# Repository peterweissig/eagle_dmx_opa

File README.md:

# project_opa
DMX control unit, based on atmel 32-bit controller

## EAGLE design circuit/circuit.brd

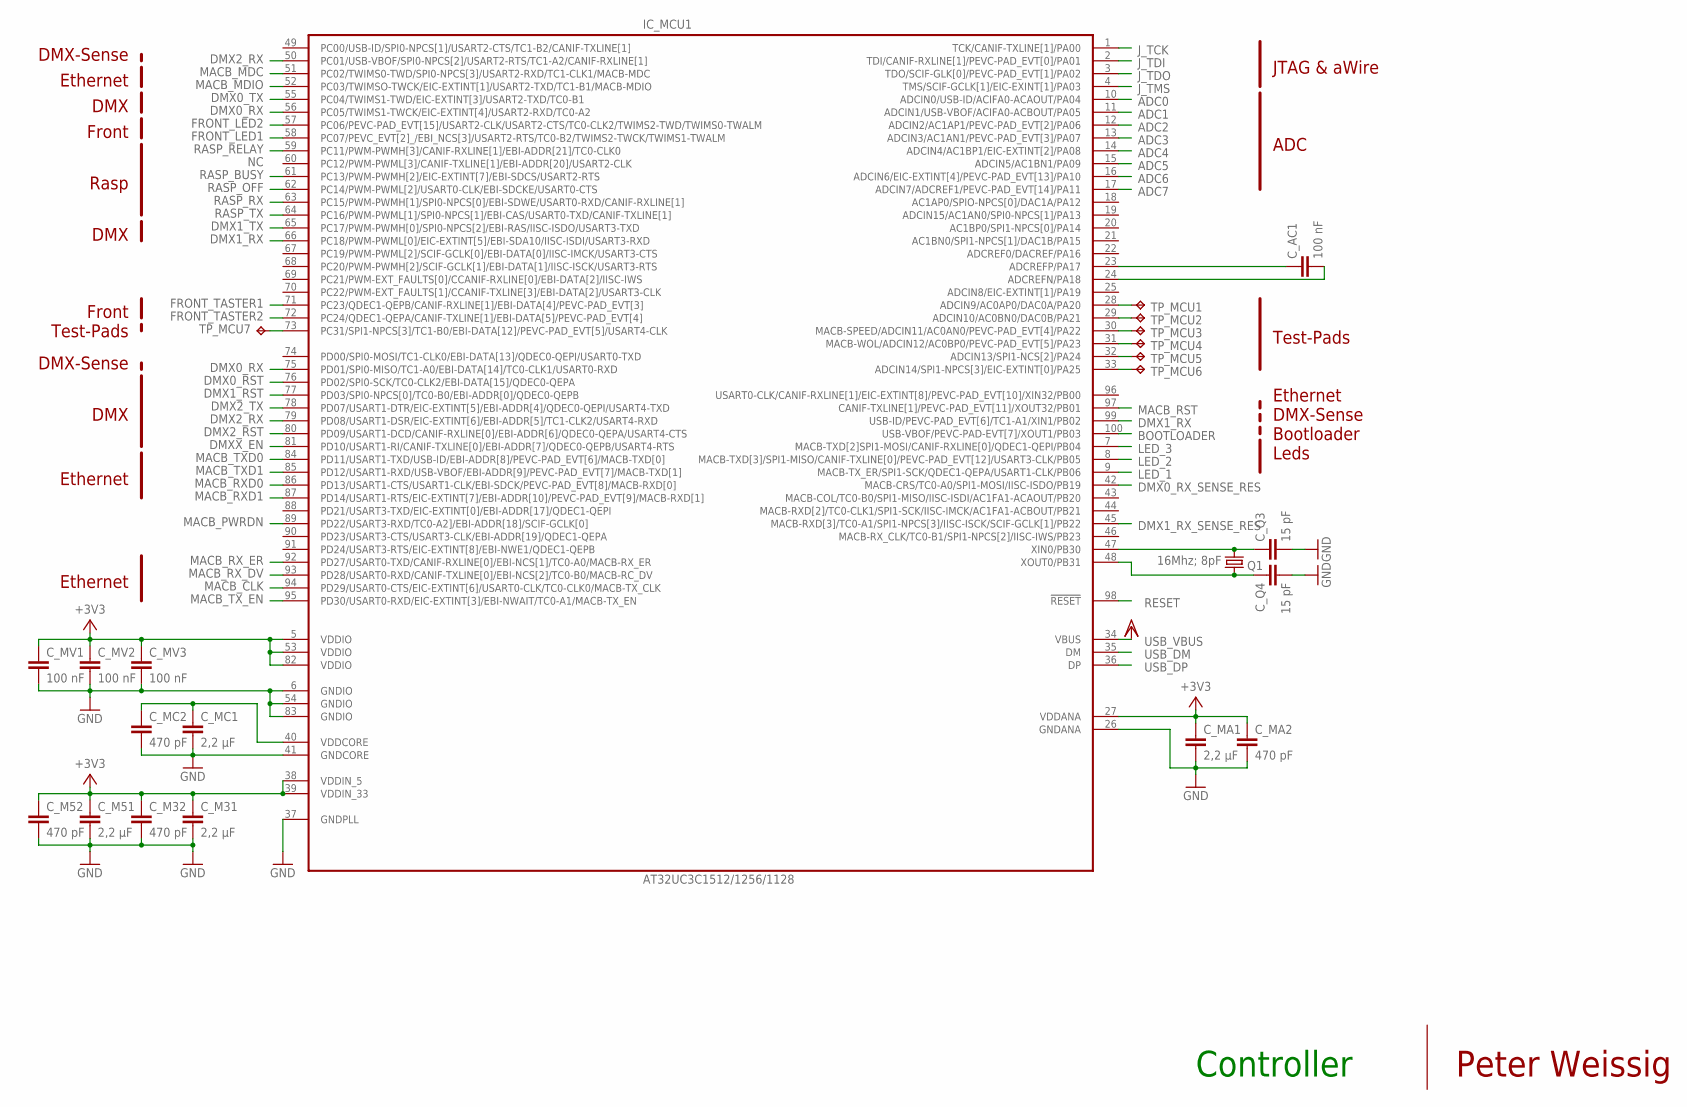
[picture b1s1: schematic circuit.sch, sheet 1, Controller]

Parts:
C_AC1: 100 nF; C0603K
C_M31, C_M51: 2,2 µF; C0603K
C_M32, C_M52: 470 pF; C0603K
C_MA1: 2,2 µF; C0603K
C_MA2: 470 pF; C0603K
C_MC1: 2,2 µF; C0603K
C_MC2: 470 pF; C0603K
C_MV1, C_MV2, C_MV3: 100 nF; C0603K
C_Q3, C_Q4: 15 pF; C0603K
IC_MCU1: AT32UC3C1512/1256/1128; TQFP100
Q1: 16Mhz; 8pF; NX5032
TP_MCU1, TP_MCU2, TP_MCU3, TP_MCU4, TP_MCU5, TP_MCU6, TP_MCU7: TPTP15R; TP15R

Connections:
+3V3: C_M31.1, C_M32.1, C_M51.1, C_M52.1, C_MA1.1, C_MA2.1, C_MV1.1, C_MV2.1, C_MV3.1, IC_MCU1.5 (VDDIO), IC_MCU1.27 (VDDANA), IC_MCU1.38 (VDDIN_5), IC_MCU1.39 (VDDIN_33), IC_MCU1.53 (VDDIO), IC_MCU1.82 (VDDIO); also elsewhere on the board
ADC0: IC_MCU1.10 (ADCIN0/USB-ID/ACIFA0-ACAOUT/PA04); also elsewhere on the board
ADC1: IC_MCU1.11 (ADCIN1/USB-VBOF/ACIFA0-ACBOUT/PA05); also elsewhere on the board
ADC2: IC_MCU1.12 (ADCIN2/AC1AP1/PEVC-PAD_EVT[2]/PA06); also elsewhere on the board
ADC3: IC_MCU1.13 (ADCIN3/AC1AN1/PEVC-PAD_EVT[3]/PA07); also elsewhere on the board
ADC4: IC_MCU1.14 (ADCIN4/AC1BP1/EIC-EXTINT[2]/PA08); also elsewhere on the board
ADC5: IC_MCU1.15 (ADCIN5/AC1BN1/PA09); also elsewhere on the board
ADC6: IC_MCU1.16 (ADCIN6/EIC-EXTINT[4]/PEVC-PAD_EVT[13]/P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); also elsewhere on the board
ADC7: IC_MCU1.17 (ADCIN7/ADCREF1/PEVC-PAD_EVT[14]/PA11); also elsewhere on the board
BOOTLOADER: IC_MCU1.100 (USB-VBOF/PEVC-PAD-EVT[7]/XOUT1/PB03); also elsewhere on the board
DMX0_RST: IC_MCU1.76 (PD02/SPI0-SCK/TC0-CLK2/EBI-DATA[15]/QDE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); also elsewhere on the board
DMX0_RX: IC_MCU1.56 (PC05/TWIMS1-TWCK/EIC-EXTINT[4]/USART2-R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), IC_MCU1.75 (PD01/SPI0-MISO/TC1-A0/EBI-DATA[14]/TC0-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); also elsewhere on the board
DMX0_RX_SENSE_RES: IC_MCU1.42 (MACB-CRS/TC0-A0/SPI1-MOSI/IISC-ISDO/PB19)
DMX0_TX: IC_MCU1.55 (PC04/TWIMS1-TWD/EIC-EXTINT[3]/USART2-TX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); also elsewhere on the board
DMX1_RST: IC_MCU1.77 (PD03/SPI0-NPCS[0]/TC0-B0/EBI-ADDR[0]/QD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); also elsewhere on the board
DMX1_RX: IC_MCU1.66 (PC18/PWM-PWML[0]/EIC-EXTINT[5]/EBI-SDA1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), IC_MCU1.99 (USB-ID/PEVC-PAD_EVT[6]/TC1-A1/XIN1/PB02); also elsewhere on the board
DMX1_RX_SENSE_RES: IC_MCU1.45 (MACB-RXD[3]/TC0-A1/SPI1-NPCS[3]/IISC-IS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)
DMX1_TX: IC_MCU1.65 (PC17/PWM-PWMH[0]/SPI0-NPCS[2]/EBI-RAS/I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); also elsewhere on the board
DMX2_RST: IC_MCU1.80 (PD09/USART1-DCD/CANIF-RXLINE[0]/EBI-ADD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); also elsewhere on the board
DMX2_RX: IC_MCU1.50 (PC01/USB-VBOF/SPI0-NPCS[2]/USART2-RTS/T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), IC_MCU1.79 (PD08/USART1-DSR/EIC-EXTINT[6]/EBI-ADDR[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); also elsewhere on the board
DMX2_TX: IC_MCU1.78 (PD07/USART1-DTR/EIC-EXTINT[5]/EBI-ADDR[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); also elsewhere on the board
DMXX_EN: IC_MCU1.81 (PD10/USART1-RI/CANIF-TXLINE[0]/EBI-ADDR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); also elsewhere on the board
FRONT_LED1: IC_MCU1.58 (PC07/PEVC_EVT[2]_/EBI_NCS[3]/USART2-RTS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); also elsewhere on the board
FRONT_LED2: IC_MCU1.57 (PC06/PEVC-PAD_EVT[15]/USART2-CLK/USART2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); also elsewhere on the board
FRONT_TASTER1: IC_MCU1.71 (PC23/QDEC1-QEPB/CANIF-RXLINE[1]/EBI-DAT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); also elsewhere on the board
FRONT_TASTER2: IC_MCU1.72 (PC24/QDEC1-QEPA/CANIF-TXLINE[1]/EBI-DAT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); also elsewhere on the board
FRONT_TASTER3: IC_MCU1.73 (PC31/SPI1-NPCS[3]/TC1-B0/EBI-DATA[12]/P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), TP_MCU7.TP
GND: C_M31.2, C_M32.2, C_M51.2, C_M52.2, C_MA1.2, C_MA2.2, C_MC1.2, C_MC2.2, C_MV1.2, C_MV2.2, C_MV3.2, C_Q3.2, C_Q4.2, IC_MCU1.6 (GNDIO), IC_MCU1.26 (GNDANA), IC_MCU1.37 (GNDPLL), IC_MCU1.41 (GNDCORE), IC_MCU1.54 (GNDIO), IC_MCU1.83 (GNDIO); also elsewhere on the board
J_TCK: IC_MCU1.1 (TCK/CANIF-TXLINE[1]/PA00); also elsewhere on the board
J_TDI: IC_MCU1.2 (TDI/CANIF-RXLINE[1]/PEVC-PAD_EVT[0]/PA01); also elsewhere on the board
J_TDO: IC_MCU1.3 (TDO/SCIF-GLK[0]/PEVC-PAD_EVT[1]/PA02); also elsewhere on the board
J_TMS: IC_MCU1.4 (TMS/SCIF-GCLK[1]/EIC-EXINT[1]/PA03); also elsewhere on the board
LED_1: IC_MCU1.9 (MACB-TX_ER/SPI1-SCK/QDEC1-QEPA/USART1-C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); also elsewhere on the board
LED_2: IC_MCU1.8 (MACB-TXD[3]/SPI1-MISO/CANIF-TXLINE[0]/P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); also elsewhere on the board
LED_3: IC_MCU1.7 (MACB-TXD[2]SPI1-MOSI/CANIF-RXLINE[0]/QD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); also elsewhere on the board
MACB_CLK: IC_MCU1.94 (PD29/USART0-CTS/EIC-EXTINT[6]/USART0-CL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); also elsewhere on the board
MACB_MDC: IC_MCU1.51 (PC02/TWIMS0-TWD/SPI0-NPCS[3]/USART2-RXD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); also elsewhere on the board
MACB_MDIO: IC_MCU1.52 (PC03/TWIMSO-TWCK/EIC-EXTINT[1]/USART2-T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); also elsewhere on the board
MACB_PWRDN: IC_MCU1.89 (PD22/USART3-RXD/TC0-A2]/EBI-ADDR[18]/SC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); also elsewhere on the board
MACB_RST: IC_MCU1.97 (CANIF-TXLINE[1]/PEVC-PAD_EVT[11]/XOUT32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); also elsewhere on the board
MACB_RXD0: IC_MCU1.86 (PD13/USART1-CTS/USART1-CLK/EBI-SDCK/PEV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); also elsewhere on the board
MACB_RXD1: IC_MCU1.87 (PD14/USART1-RTS/EIC-EXTINT[7]/EBI-ADDR[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); also elsewhere on the board
MACB_RX_DV: IC_MCU1.93 (PD28/USART0-RXD/CANIF-TXLINE[0]/EBI-NCS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); also elsewhere on the board
MACB_RX_ER: IC_MCU1.92 (PD27/USART0-TXD/CANIF-RXLINE[0]/EBI-NCS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); also elsewhere on the board
MACB_TXD0: IC_MCU1.84 (PD11/USART1-TXD/USB-ID/EBI-ADDR[8]/PEVC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); also elsewhere on the board
MACB_TXD1: IC_MCU1.85 (PD12/USART1-RXD/USB-VBOF/EBI-ADDR[9]/PE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); also elsewhere on the board
MACB_TX_EN: IC_MCU1.95 (PD30/USART0-RXD/EIC-EXTINT[3]/EBI-NWAIT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); also elsewhere on the board
unnamed: C_MC1.1, C_MC2.1, IC_MCU1.40 (VDDCORE)
unnamed: C_Q3.1, IC_MCU1.47 (XIN0/PB30), Q1.2
unnamed: IC_MCU1.28 (ADCIN9/AC0AP0/DAC0A/PA20), TP_MCU1.TP
unnamed: C_Q4.1, IC_MCU1.48 (XOUT0/PB31), Q1.1
unnamed: IC_MCU1.29 (ADCIN10/AC0BN0/DAC0B/PA21), TP_MCU2.TP
unnamed: IC_MCU1.30 (MACB-SPEED/ADCIN11/AC0AN0/PEVC-PAD_EVT[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), TP_MCU3.TP
unnamed: C_AC1.1, IC_MCU1.23 (ADCREFP/PA17)
unnamed: C_AC1.2, IC_MCU1.24 (ADCREFN/PA18)
unnamed: IC_MCU1.31 (MACB-WOL/ADCIN12/AC0BP0/PEVC-PAD_EVT[5]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), TP_MCU4.TP
unnamed: IC_MCU1.32 (ADCIN13/SPI1-NCS[2]/PA24), TP_MCU5.TP
unnamed: IC_MCU1.33 (ADCIN14/SPI1-NPCS[3]/EIC-EXTINT[0]/PA25), TP_MCU6.TP
RASP_BUSY: IC_MCU1.61 (PC13/PWM-PWMH[2]/EIC-EXTINT[7]/EBI-SDCS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); also elsewhere on the board
RASP_OFF: IC_MCU1.62 (PC14/PWM-PWML[2]/USART0-CLK/EBI-SDCKE/U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); also elsewhere on the board
RASP_RELAY: IC_MCU1.59 (PC11/PWM-PWMH[3]/CANIF-RXLINE[1]/EBI-AD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); also elsewhere on the board
RASP_RX: IC_MCU1.63 (PC15/PWM-PWMH[1]/SPI0-NPCS[0]/EBI-SDWE/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); also elsewhere on the board
RASP_TX: IC_MCU1.64 (PC16/PWM-PWML[1]/SPI0-NPCS[1]/EBI-CAS/U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); also elsewhere on the board
RESET: IC_MCU1.98 (!RESET); also elsewhere on the board
USB_DM: IC_MCU1.35 (DM); also elsewhere on the board
USB_DP: IC_MCU1.36 (DP); also elsewhere on the board
USB_VBUS: IC_MCU1.34 (VBUS); also elsewhere on the board

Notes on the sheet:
Controller
Peter Weissig
JTAG & aWire
ADC
Ethernet
DMX
Rasp
DMX-Sense
Leds
Bootloader
Test-Pads
Front

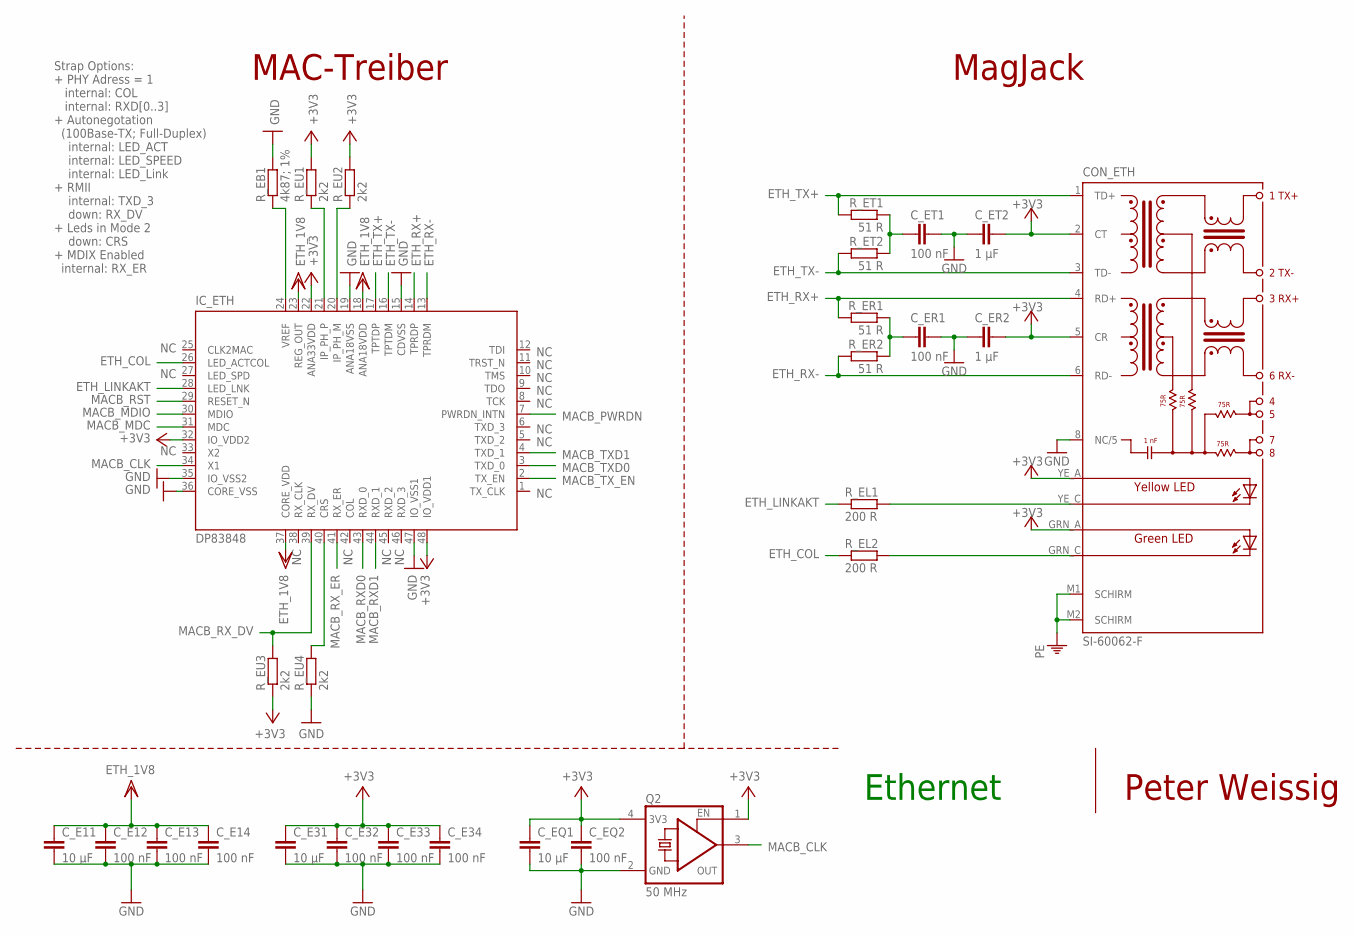
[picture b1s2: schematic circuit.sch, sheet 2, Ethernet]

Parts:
CON_ETH: SI-60062-F; MAG_JACK
C_E11, C_E31: 10 µF; C0603
C_E12, C_E13, C_E14, C_E32, C_E33, C_E34: 100 nF; C0603
C_EQ1: 10 µF; C0603
C_EQ2: 100 nF; C0603
C_ER1: 100 nF; C0603
C_ER2: 1 µF; C0603
C_ET1: 100 nF; C0603
C_ET2: 1 µF; C0603
IC_ETH: DP83848; LQFP48
Q2: 50 MHz; XO53
R_EB1: 4k87; 1%; R0603
R_EL1, R_EL2: 200 R; R0603
R_ER1, R_ER2: 51 R; R0603
R_ET1, R_ET2: 51 R; R0603
R_EU1, R_EU2, R_EU3, R_EU4: 2k2; R0603

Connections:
+3V3: CON_ETH.2 (CT), CON_ETH.5 (CR), CON_ETH.GRN_A (AL), CON_ETH.YE_A (A-R), C_E31.1, C_E32.1, C_E33.1, C_E34.1, C_EQ1.1, C_EQ2.1, C_ER2.2, C_ET2.2, IC_ETH.22 (ANA33VDD), IC_ETH.32 (IO_VDD2), IC_ETH.48 (IO_VDD1), Q2.1 (EN), Q2.4 (3V3), R_EU1.2, R_EU2.2, R_EU3.1; also elsewhere on the board
ETH_1V8: C_E11.1, C_E12.1, C_E13.1, C_E14.1, IC_ETH.18 (ANA18VDD), IC_ETH.23 (REG_OUT), IC_ETH.37 (CORE_VDD)
ETH_COL: IC_ETH.26 (LED_ACTCOL), R_EL2.1
ETH_LINKAKT: IC_ETH.28 (LED_LNK), R_EL1.1
ETH_RX+: CON_ETH.4 (RD+), IC_ETH.14 (TPRDP), R_ER1.2
ETH_RX-: CON_ETH.6 (RD-), IC_ETH.13 (TPRDM), R_ER2.2
ETH_TX+: CON_ETH.1 (TD+), IC_ETH.17 (TPTDP), R_ET1.2
ETH_TX-: CON_ETH.3 (TD-), IC_ETH.16 (TPTDM), R_ET2.2
GND: CON_ETH.8 (NC/5), C_E11.2, C_E12.2, C_E13.2, C_E14.2, C_E31.2, C_E32.2, C_E33.2, C_E34.2, C_EQ1.2, C_EQ2.2, C_ER1.2, C_ER2.1, C_ET1.2, C_ET2.1, IC_ETH.15 (CDVSS), IC_ETH.19 (ANA18VSS), IC_ETH.35 (IO_VSS2), IC_ETH.36 (CORE_VSS), IC_ETH.47 (IO_VSS1), Q2.2 (GND), R_EB1.2, R_EU4.1; also elsewhere on the board
MACB_CLK: IC_ETH.34 (X1), Q2.3 (OUT); also elsewhere on the board
MACB_MDC: IC_ETH.31 (MDC); also elsewhere on the board
MACB_MDIO: IC_ETH.30 (MDIO); also elsewhere on the board
MACB_PWRDN: IC_ETH.7 (PWRDN_INTN); also elsewhere on the board
MACB_RST: IC_ETH.29 (RESET_N); also elsewhere on the board
MACB_RXD0: IC_ETH.43 (RXD_0); also elsewhere on the board
MACB_RXD1: IC_ETH.44 (RXD_1); also elsewhere on the board
MACB_RX_DV: IC_ETH.39 (RX_DV), R_EU3.2; also elsewhere on the board
MACB_RX_ER: IC_ETH.41 (RX_ER); also elsewhere on the board
MACB_TXD0: IC_ETH.3 (TXD_0); also elsewhere on the board
MACB_TXD1: IC_ETH.4 (TXD_1); also elsewhere on the board
MACB_TX_EN: IC_ETH.2 (TX_EN); also elsewhere on the board
unnamed: IC_ETH.24 (VREF), R_EB1.1
unnamed: IC_ETH.21 (IP_PH_P), R_EU1.1
unnamed: IC_ETH.20 (IP_PH_M), R_EU2.1
unnamed: IC_ETH.40 (CRS), R_EU4.2
unnamed: CON_ETH.YE_C (C-R), R_EL1.2
unnamed: CON_ETH.GRN_C (C-L), R_EL2.2
unnamed: C_ER1.1, R_ER1.1, R_ER2.1
unnamed: C_ET1.1, R_ET1.1, R_ET2.1
PE: CON_ETH.M1 (SCHIRM), CON_ETH.M2 (SCHIRM); also elsewhere on the board

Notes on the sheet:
Ethernet
Peter Weissig
MagJack
MAC-Treiber
ETH_1V8
Strap Options: + PHY Adress = 1 internal: COL internal: RXD[0..3] + Autonegotation (100Base-TX; Full-Duplex) internal: LED_ACT internal: LED_SPEED internal: LED_Link + RMII internal: TXD_3 down: RX_DV + Leds in Mode 2 down: CRS + MDIX Enabled internal: RX_ER

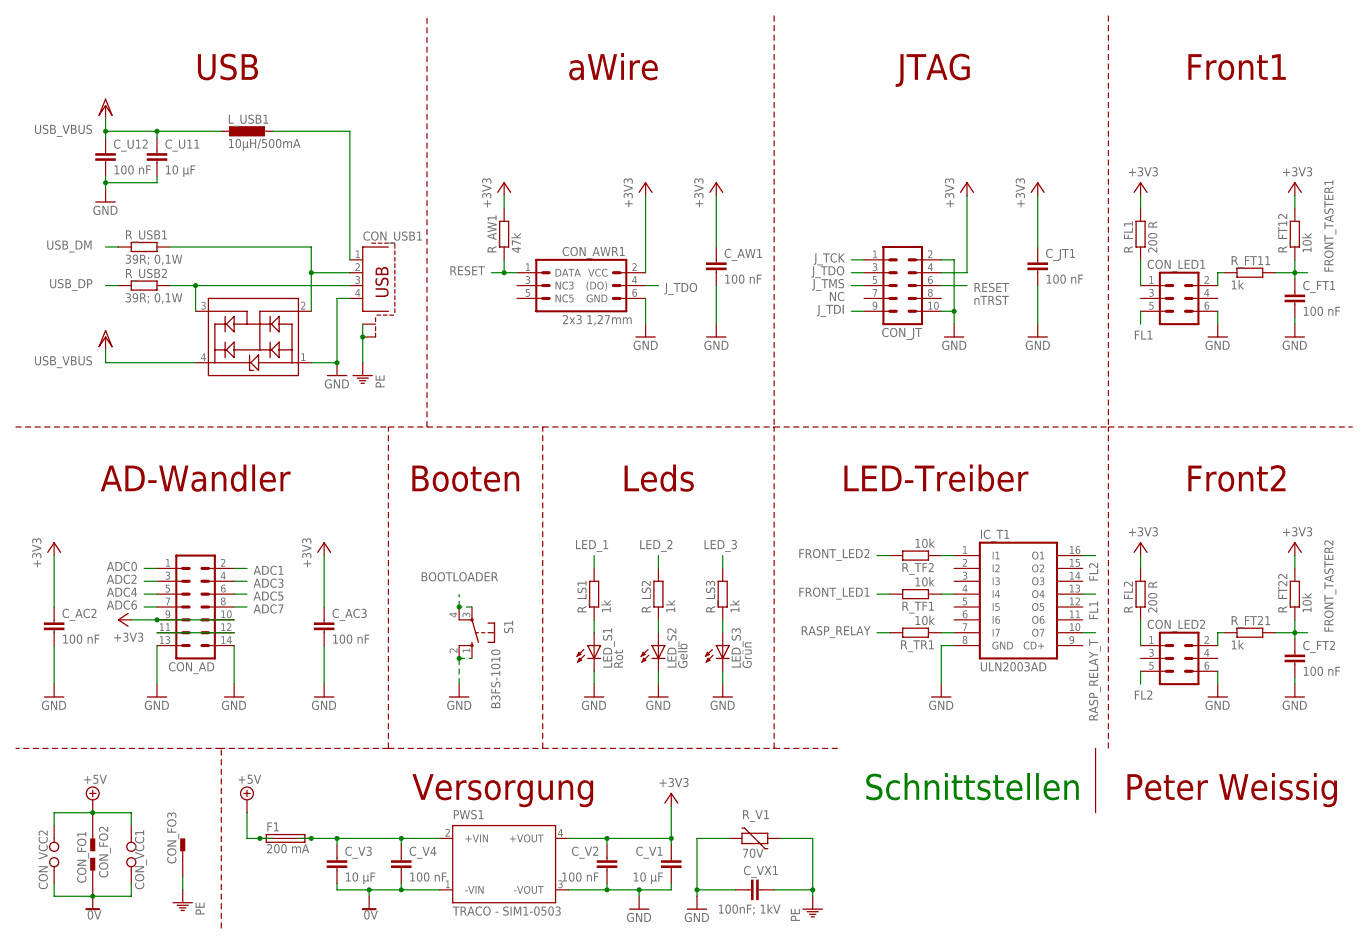
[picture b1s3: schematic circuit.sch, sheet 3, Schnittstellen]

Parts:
CON_AD: ML14
CON_AWR1: 2x3 1,27mm; 2X3_MINI
CON_FO1, CON_FO2, CON_FO3: PIN2F061.100; F061.100
CON_JT: ML10
CON_LED1, CON_LED2: ML6
CON_USB1: PN61729-S
CON_VCC1, CON_VCC2: W237-02P; W237-132
C_AC2, C_AC3: 100 nF; C0603K
C_AW1: 100 nF; C0603K
C_FT1, C_FT2: 100 nF; C0603K
C_JT1: 100 nF; C0603K
C_U11: 10 µF; C0805K
C_U12: 100 nF; C0603K
C_V1, C_V3: 10 µF; C0603K
C_V2, C_V4: 100 nF; C0603K
C_VX1: 100nF; 1kV; C1812K
D1: PRTR5V0U2X; SOT143-R
F1: 200 mA; SHK20L
IC_T1: ULN2003AD; SO16
LED_S1: Rot; CHIPLED_1206
LED_S2: Gelb; CHIPLED_1206
LED_S3: Grün; CHIPLED_1206
L_USB1: 10µH/500mA; L1210
PWS1: TRACO - SIM1-0503; TRACO_TME_1
R_AW1: 47k; R0603
R_FL1, R_FL2: 200 R; R0603
R_FT11, R_FT21: 1k; R0603
R_FT12, R_FT22: 10k; R0603
R_LS1, R_LS2, R_LS3: 1k; R0603
R_TF1, R_TF2: 10k; R0603
R_TR1: 10k; R0603
R_USB1, R_USB2: 39R; 0,1W; R0603
R_V1: 70V; CT/CN1206
S1: B3FS-1010; B3F-10XX

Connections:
0V: CON_FO1.A1, CON_FO1.A2, CON_VCC1.2, CON_VCC2.2, C_V3.2, C_V4.2, PWS1.1 (-VIN); also elsewhere on the board
+3V3: CON_AD.9, CON_AD.10, CON_AWR1.2 (VCC), CON_JT.4, C_AC2.1, C_AC3.1, C_AW1.1, C_JT1.1, C_V1.1, C_V2.1, PWS1.4 (+VOUT), R_AW1.2, R_FL1.2, R_FL2.2, R_FT12.2, R_FT22.2; also elsewhere on the board
+5V: CON_FO2.A1, CON_FO2.A2, CON_VCC1.1, CON_VCC2.1, F1.1A, F1.1B; also elsewhere on the board
ADC0: CON_AD.1; also elsewhere on the board
ADC1: CON_AD.2; also elsewhere on the board
ADC2: CON_AD.3; also elsewhere on the board
ADC3: CON_AD.4; also elsewhere on the board
ADC4: CON_AD.5; also elsewhere on the board
ADC5: CON_AD.6; also elsewhere on the board
ADC6: CON_AD.7; also elsewhere on the board
ADC7: CON_AD.8; also elsewhere on the board
BOOTLOADER: S1.3, S1.4 (P1); also elsewhere on the board
FL1: CON_LED1.5, IC_T1.13 (O4)
FL2: CON_LED2.5, IC_T1.16 (O1)
FRONT_LED1: R_TF1.2; also elsewhere on the board
FRONT_LED2: R_TF2.2; also elsewhere on the board
FRONT_TASTER1: C_FT1.1, R_FT11.2, R_FT12.1; also elsewhere on the board
FRONT_TASTER2: C_FT2.1, R_FT21.2, R_FT22.1; also elsewhere on the board
GND: CON_AD.13, CON_AD.14, CON_AWR1.6 (GND), CON_JT.2, CON_JT.10, CON_LED1.6, CON_LED2.6, CON_USB1.4, C_AC2.2, C_AC3.2, C_AW1.2, C_FT1.2, C_FT2.2, C_JT1.2, C_U11.2, C_U12.2, C_V1.2, C_V2.2, C_VX1.1, D1.1 (GND), IC_T1.8 (GND), LED_S1.C, LED_S2.C, LED_S3.C, PWS1.3 (-VOUT), R_V1.2, S1.1 (S), S1.2 (S1); also elsewhere on the board
J_TCK: CON_JT.1; also elsewhere on the board
J_TDI: CON_JT.9; also elsewhere on the board
J_TDO: CON_AWR1.4 ((DO)), CON_JT.3; also elsewhere on the board
J_TMS: CON_JT.5; also elsewhere on the board
LED_1: R_LS1.2; also elsewhere on the board
LED_2: R_LS2.2; also elsewhere on the board
LED_3: R_LS3.2; also elsewhere on the board
unnamed: LED_S1.A, R_LS1.1
unnamed: LED_S2.A, R_LS2.1
unnamed: CON_USB1.3, D1.3 (IN/OUT2), R_USB2.2
unnamed: CON_USB1.2, D1.2 (IN/OUT1), R_USB1.2
unnamed: LED_S3.A, R_LS3.1
unnamed: CON_USB1.1, L_USB1.1
unnamed: CON_AD.11, CON_AD.12
unnamed: IC_T1.4 (I4), R_TF1.1
unnamed: CON_LED1.1, R_FL1.1
unnamed: C_V3.1, C_V4.1, F1.2A, F1.2B, PWS1.2 (+VIN)
unnamed: CON_LED1.2, R_FT11.1
unnamed: CON_LED2.1, R_FL2.1
unnamed: CON_LED2.2, R_FT21.1
unnamed: IC_T1.1 (I1), R_TF2.1
unnamed: IC_T1.7 (I7), R_TR1.1
PE: CON_FO3.A1, CON_FO3.A2, CON_USB1.S1, CON_USB1.S2, C_VX1.2, R_V1.1; also elsewhere on the board
RASP_RELAY: R_TR1.2; also elsewhere on the board
RASP_RELAY_T: IC_T1.10 (O7); also elsewhere on the board
RESET: CON_AWR1.1 (DATA), CON_JT.6, R_AW1.1; also elsewhere on the board
USB_DM: R_USB1.1; also elsewhere on the board
USB_DP: R_USB2.1; also elsewhere on the board
USB_VBUS: C_U11.1, C_U12.1, D1.4 (VDD), L_USB1.2; also elsewhere on the board

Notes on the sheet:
Schnittstellen
USB
Leds
aWire
Booten
Peter Weissig
AD-Wandler
Versorgung
JTAG
nTRST
CON_VCC2
CON_VCC1
LED-Treiber
Front2
Front1

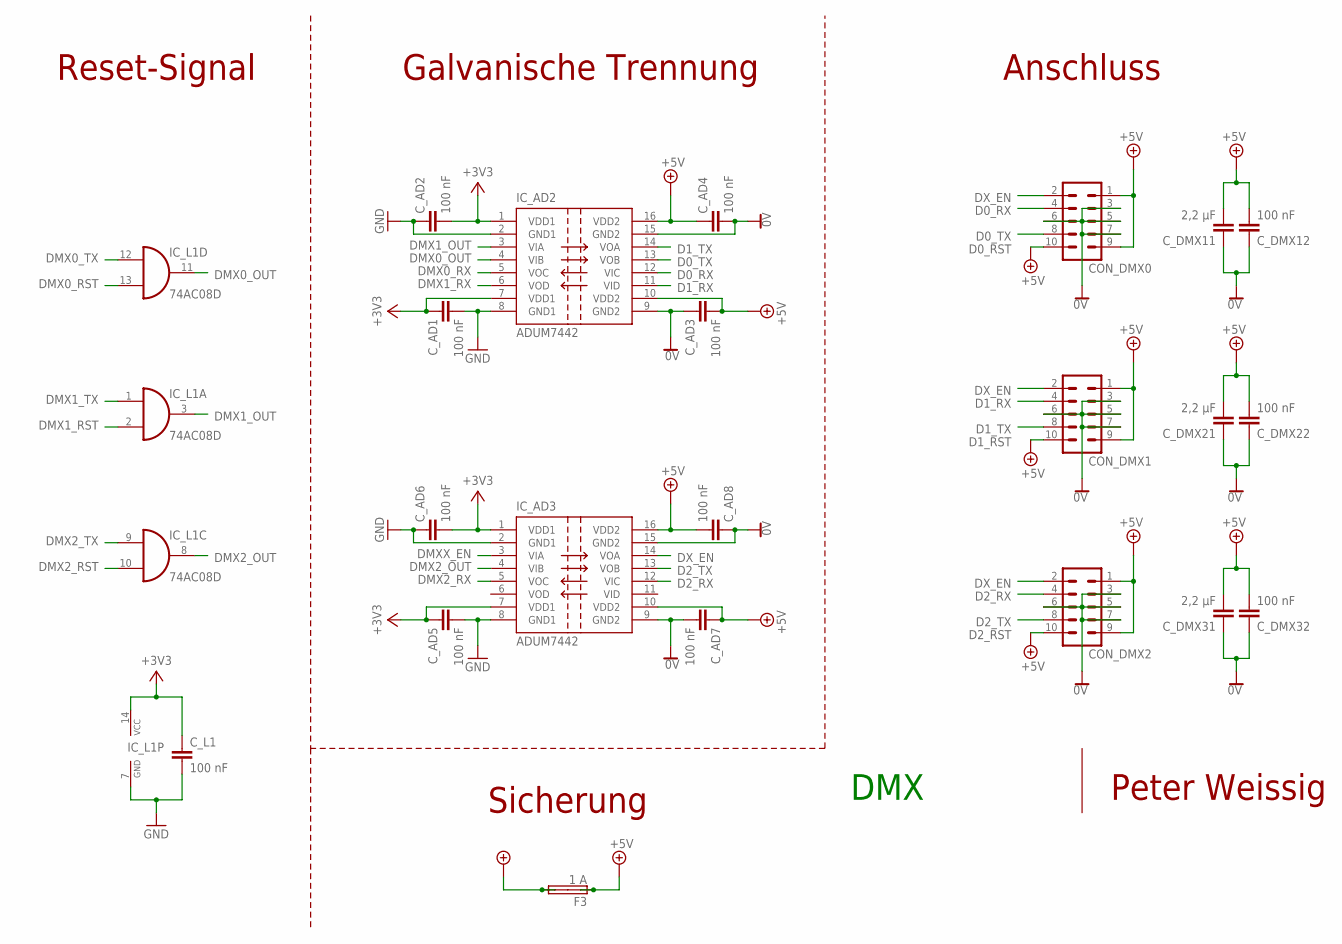
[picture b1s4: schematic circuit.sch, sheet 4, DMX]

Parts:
CON_DMX0, CON_DMX1, CON_DMX2: ML10
C_AD1, C_AD2, C_AD3, C_AD4, C_AD5, C_AD6, C_AD7, C_AD8: 100 nF; C0603K
C_DMX11, C_DMX21, C_DMX31: 2,2 µF; C0603K
C_DMX12, C_DMX22, C_DMX32: 100 nF; C0603K
C_L1: 100 nF; C0603K
F3: 1 A; SHK20L
IC_AD2, IC_AD3: ADUM7442; SOP64P600X175-16N
IC_L1: 74AC08D; SO14

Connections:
0V: CON_DMX0.3, CON_DMX0.5, CON_DMX0.6, CON_DMX0.7, CON_DMX1.3, CON_DMX1.5, CON_DMX1.6, CON_DMX1.7, CON_DMX2.3, CON_DMX2.5, CON_DMX2.6, CON_DMX2.7, C_AD3.1, C_AD4.2, C_AD7.2, C_AD8.1, C_DMX11.1, C_DMX12.1, C_DMX21.1, C_DMX22.1, C_DMX31.1, C_DMX32.1, IC_AD2.9 (GND2), IC_AD2.15 (GND2), IC_AD3.9 (GND2), IC_AD3.15 (GND2); also elsewhere on the board
+3V3: C_AD1.1, C_AD2.2, C_AD5.1, C_AD6.2, C_L1.1, IC_AD2.1 (VDD1), IC_AD2.7 (VDD1), IC_AD3.1 (VDD1), IC_AD3.7 (VDD1), IC_L1.14 (VCC); also elsewhere on the board
+5V: F3.2A, F3.2B; also elsewhere on the board
D0_RX: CON_DMX0.4, IC_AD2.12 (VIC)
D0_TX: CON_DMX0.8, IC_AD2.13 (VOB)
D1_RX: CON_DMX1.4, IC_AD2.11 (VID)
D1_TX: CON_DMX1.8, IC_AD2.14 (VOA)
D2_RX: CON_DMX2.4, IC_AD3.12 (VIC)
D2_TX: CON_DMX2.8, IC_AD3.13 (VOB)
DMX0_OUT: IC_AD2.4 (VIB), IC_L1.11 (O)
DMX0_RST: IC_L1.13 (I1); also elsewhere on the board
DMX0_RX: IC_AD2.5 (VOC); also elsewhere on the board
DMX0_TX: IC_L1.12 (I0); also elsewhere on the board
DMX1_OUT: IC_AD2.3 (VIA), IC_L1.3 (O)
DMX1_RST: IC_L1.2 (I1); also elsewhere on the board
DMX1_RX: IC_AD2.6 (VOD); also elsewhere on the board
DMX1_TX: IC_L1.1 (I0); also elsewhere on the board
DMX2_OUT: IC_AD3.4 (VIB), IC_L1.8 (O)
DMX2_RST: IC_L1.10 (I1); also elsewhere on the board
DMX2_RX: IC_AD3.5 (VOC); also elsewhere on the board
DMX2_TX: IC_L1.9 (I0); also elsewhere on the board
DMXX_EN: IC_AD3.3 (VIA); also elsewhere on the board
DV_5V: CON_DMX0.1, CON_DMX0.9, CON_DMX0.10, CON_DMX1.1, CON_DMX1.9, CON_DMX1.10, CON_DMX2.1, CON_DMX2.9, CON_DMX2.10, C_AD3.2, C_AD4.1, C_AD7.1, C_AD8.2, C_DMX11.2, C_DMX12.2, C_DMX21.2, C_DMX22.2, C_DMX31.2, C_DMX32.2, F3.1A, F3.1B, IC_AD2.10 (VDD2), IC_AD2.16 (VDD2), IC_AD3.10 (VDD2), IC_AD3.16 (VDD2)
DX_EN: CON_DMX0.2, CON_DMX1.2, CON_DMX2.2, IC_AD3.14 (VOA)
GND: C_AD1.2, C_AD2.1, C_AD5.2, C_AD6.1, C_L1.2, IC_AD2.2 (GND1), IC_AD2.8 (GND1), IC_AD3.2 (GND1), IC_AD3.8 (GND1), IC_L1.7 (GND); also elsewhere on the board

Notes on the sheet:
DMX
Peter Weissig
Galvanische Trennung
D0_RST
D1_RST
D2_RST
Anschluss
Reset-Signal
Sicherung

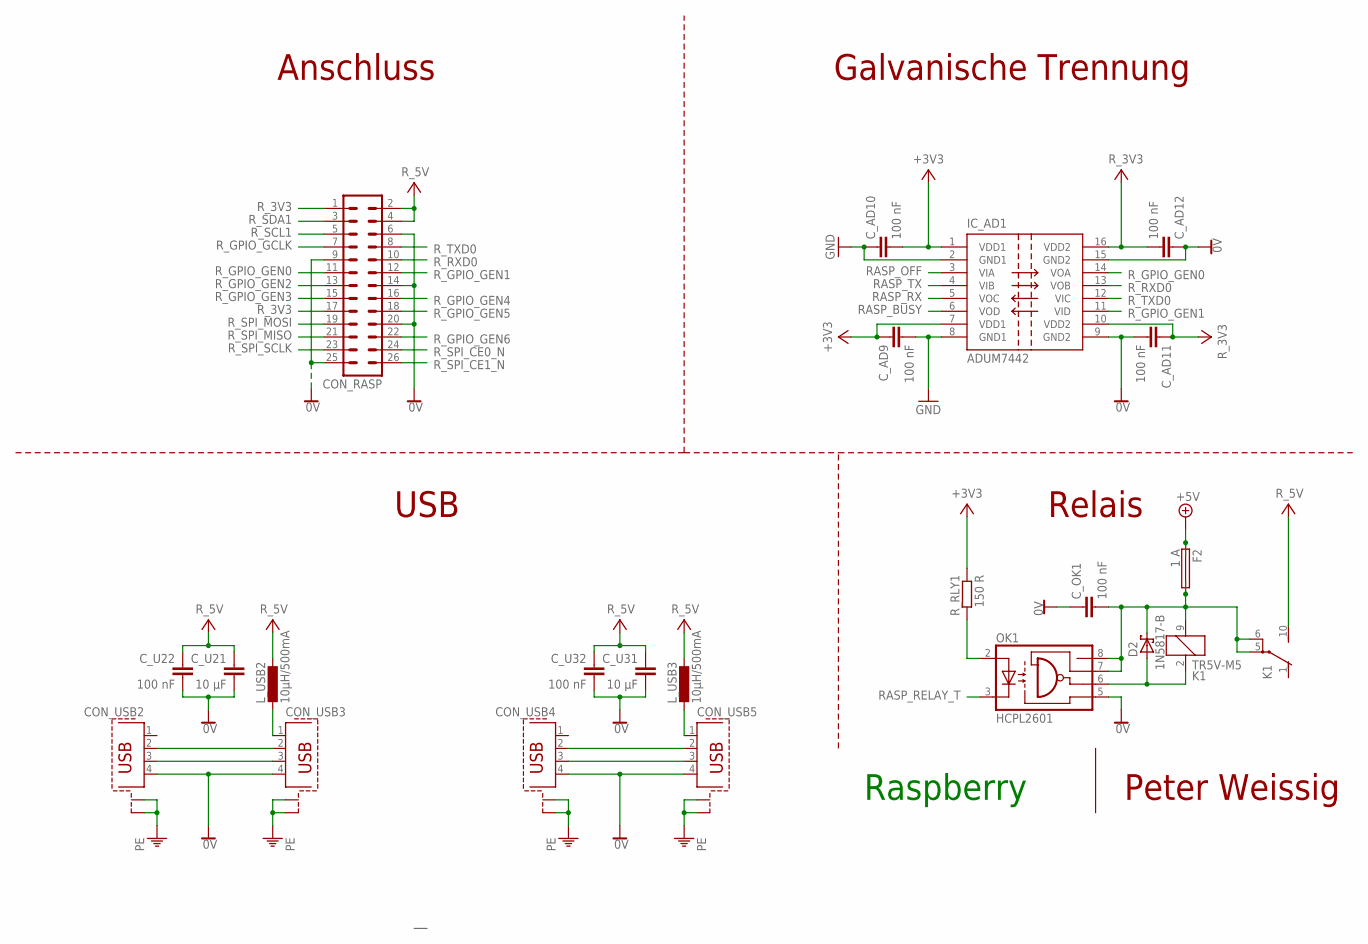
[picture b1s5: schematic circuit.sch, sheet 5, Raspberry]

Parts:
CON_RASP: ML26
CON_USB2, CON_USB4: PN61729-S
CON_USB3, CON_USB5: PN87520-S
C_AD9, C_AD10, C_AD11, C_AD12: 100 nF; C0603K
C_OK1: 100 nF; C0603K
C_U21, C_U31: 10 µF; C0805K
C_U22, C_U32: 100 nF; C0603K
D2: 1N5817-B; DO41-7.6
F2: 1 A; SHK20L
IC_AD1: ADUM7442; SOP64P600X175-16N
K1: TR5V-M5; G5V1
L_USB2, L_USB3: 10µH/500mA; L1210
OK1: HCPL2601; DIL08
R_RLY1: 150 R; R0603

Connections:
0V: CON_RASP.6, CON_RASP.9, CON_RASP.14, CON_RASP.20, CON_RASP.25, CON_USB2.4, CON_USB3.4, CON_USB4.4, CON_USB5.4, C_AD11.2, C_AD12.1, C_OK1.1, C_U21.2, C_U22.2, C_U31.2, C_U32.2, IC_AD1.9 (GND2), IC_AD1.15 (GND2), OK1.5 (GND); also elsewhere on the board
+3V3: C_AD9.1, C_AD10.2, IC_AD1.1 (VDD1), IC_AD1.7 (VDD1), R_RLY1.1; also elsewhere on the board
+5V: F2.1A, F2.1B; also elsewhere on the board
GND: C_AD9.2, C_AD10.1, IC_AD1.2 (GND1), IC_AD1.8 (GND1); also elsewhere on the board
unnamed: D2.A, K1.2 (1), OK1.6 (OUT)
unnamed: CON_USB4.2, CON_USB5.2
unnamed: CON_USB2.2, CON_USB3.2
unnamed: CON_USB2.3, CON_USB3.3
unnamed: CON_USB4.3, CON_USB5.3
unnamed: OK1.2 (A), R_RLY1.2
unnamed: CON_USB5.1, L_USB3.2
unnamed: CON_USB3.1, L_USB2.2
unnamed: C_OK1.2, D2.C, F2.2A, F2.2B, K1.5, K1.6, K1.9 (2), OK1.7 (EN), OK1.8 (VCC)
PE: CON_USB2.S1, CON_USB2.S2, CON_USB3.S1, CON_USB3.S2, CON_USB4.S1, CON_USB4.S2, CON_USB5.S1, CON_USB5.S2; also elsewhere on the board
RASP_BUSY: IC_AD1.6 (VOD); also elsewhere on the board
RASP_OFF: IC_AD1.3 (VIA); also elsewhere on the board
RASP_RELAY_T: OK1.3 (C); also elsewhere on the board
RASP_RX: IC_AD1.5 (VOC); also elsewhere on the board
RASP_TX: IC_AD1.4 (VIB); also elsewhere on the board
R_3V3: CON_RASP.1, CON_RASP.17, C_AD11.1, C_AD12.2, IC_AD1.10 (VDD2), IC_AD1.16 (VDD2)
R_5V: CON_RASP.2, CON_RASP.4, C_U21.1, C_U22.1, C_U31.1, C_U32.1, K1.10 (S), L_USB2.1, L_USB3.1
R_GPIO_GCLK: CON_RASP.7
R_GPIO_GEN0: CON_RASP.11, IC_AD1.14 (VOA)
R_GPIO_GEN1: CON_RASP.12, IC_AD1.11 (VID)
R_GPIO_GEN2: CON_RASP.13
R_GPIO_GEN3: CON_RASP.15
R_GPIO_GEN4: CON_RASP.16
R_GPIO_GEN5: CON_RASP.18
R_GPIO_GEN6: CON_RASP.22
R_RXD0: CON_RASP.10, IC_AD1.13 (VOB)
R_SCL1: CON_RASP.5
R_SDA1: CON_RASP.3
R_SPI_CE0_N: CON_RASP.24
R_SPI_CE1_N: CON_RASP.26
R_SPI_MISO: CON_RASP.21
R_SPI_MOSI: CON_RASP.19
R_SPI_SCLK: CON_RASP.23
R_TXD0: CON_RASP.8, IC_AD1.12 (VIC)

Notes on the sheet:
Raspberry
Peter Weissig
Anschluss
Galvanische Trennung
Relais
USB

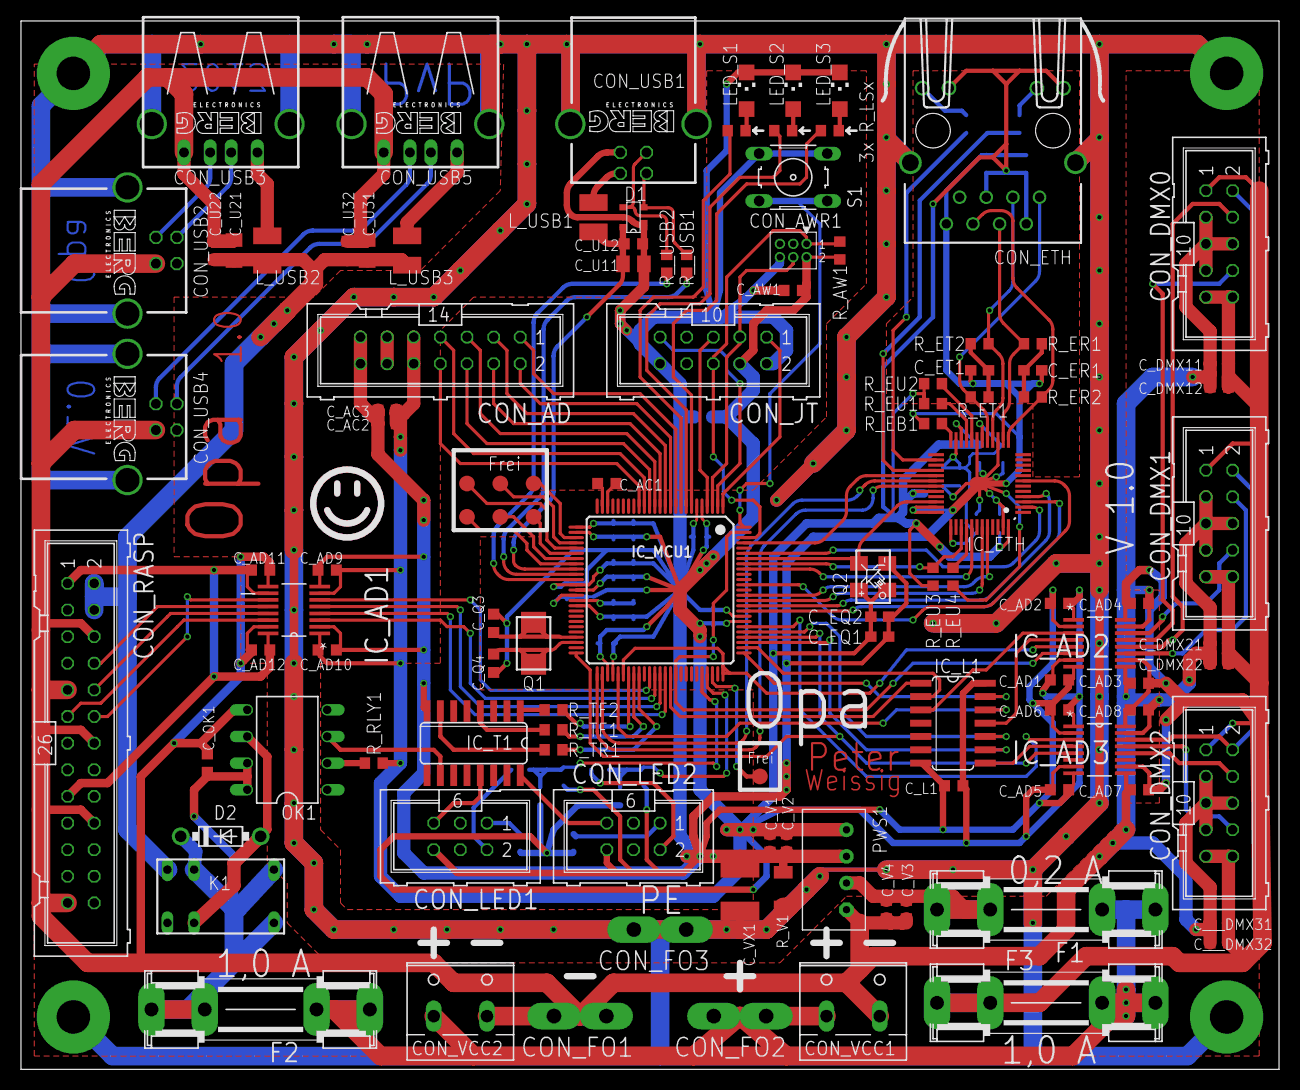
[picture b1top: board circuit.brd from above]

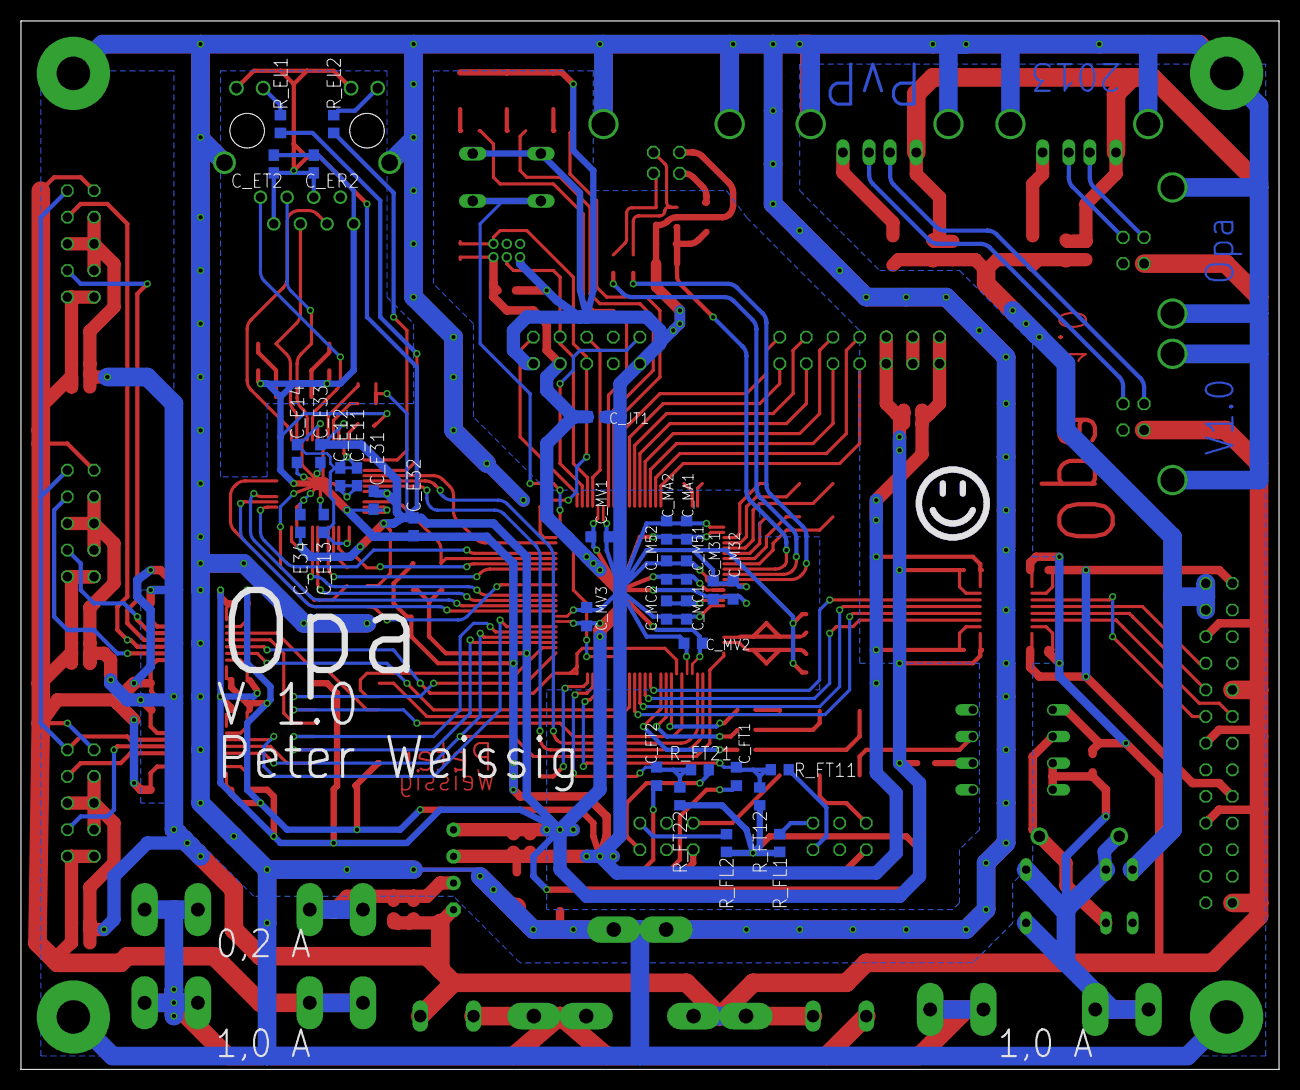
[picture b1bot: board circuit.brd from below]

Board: 2 copper layers, 120.0 x 100.0 mm, 144 parts (32 on the bottom side), 127 nets.

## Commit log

2018-02-25 changed file structure added drawings added images
2018-02-25 added better sketch of rear measurements
